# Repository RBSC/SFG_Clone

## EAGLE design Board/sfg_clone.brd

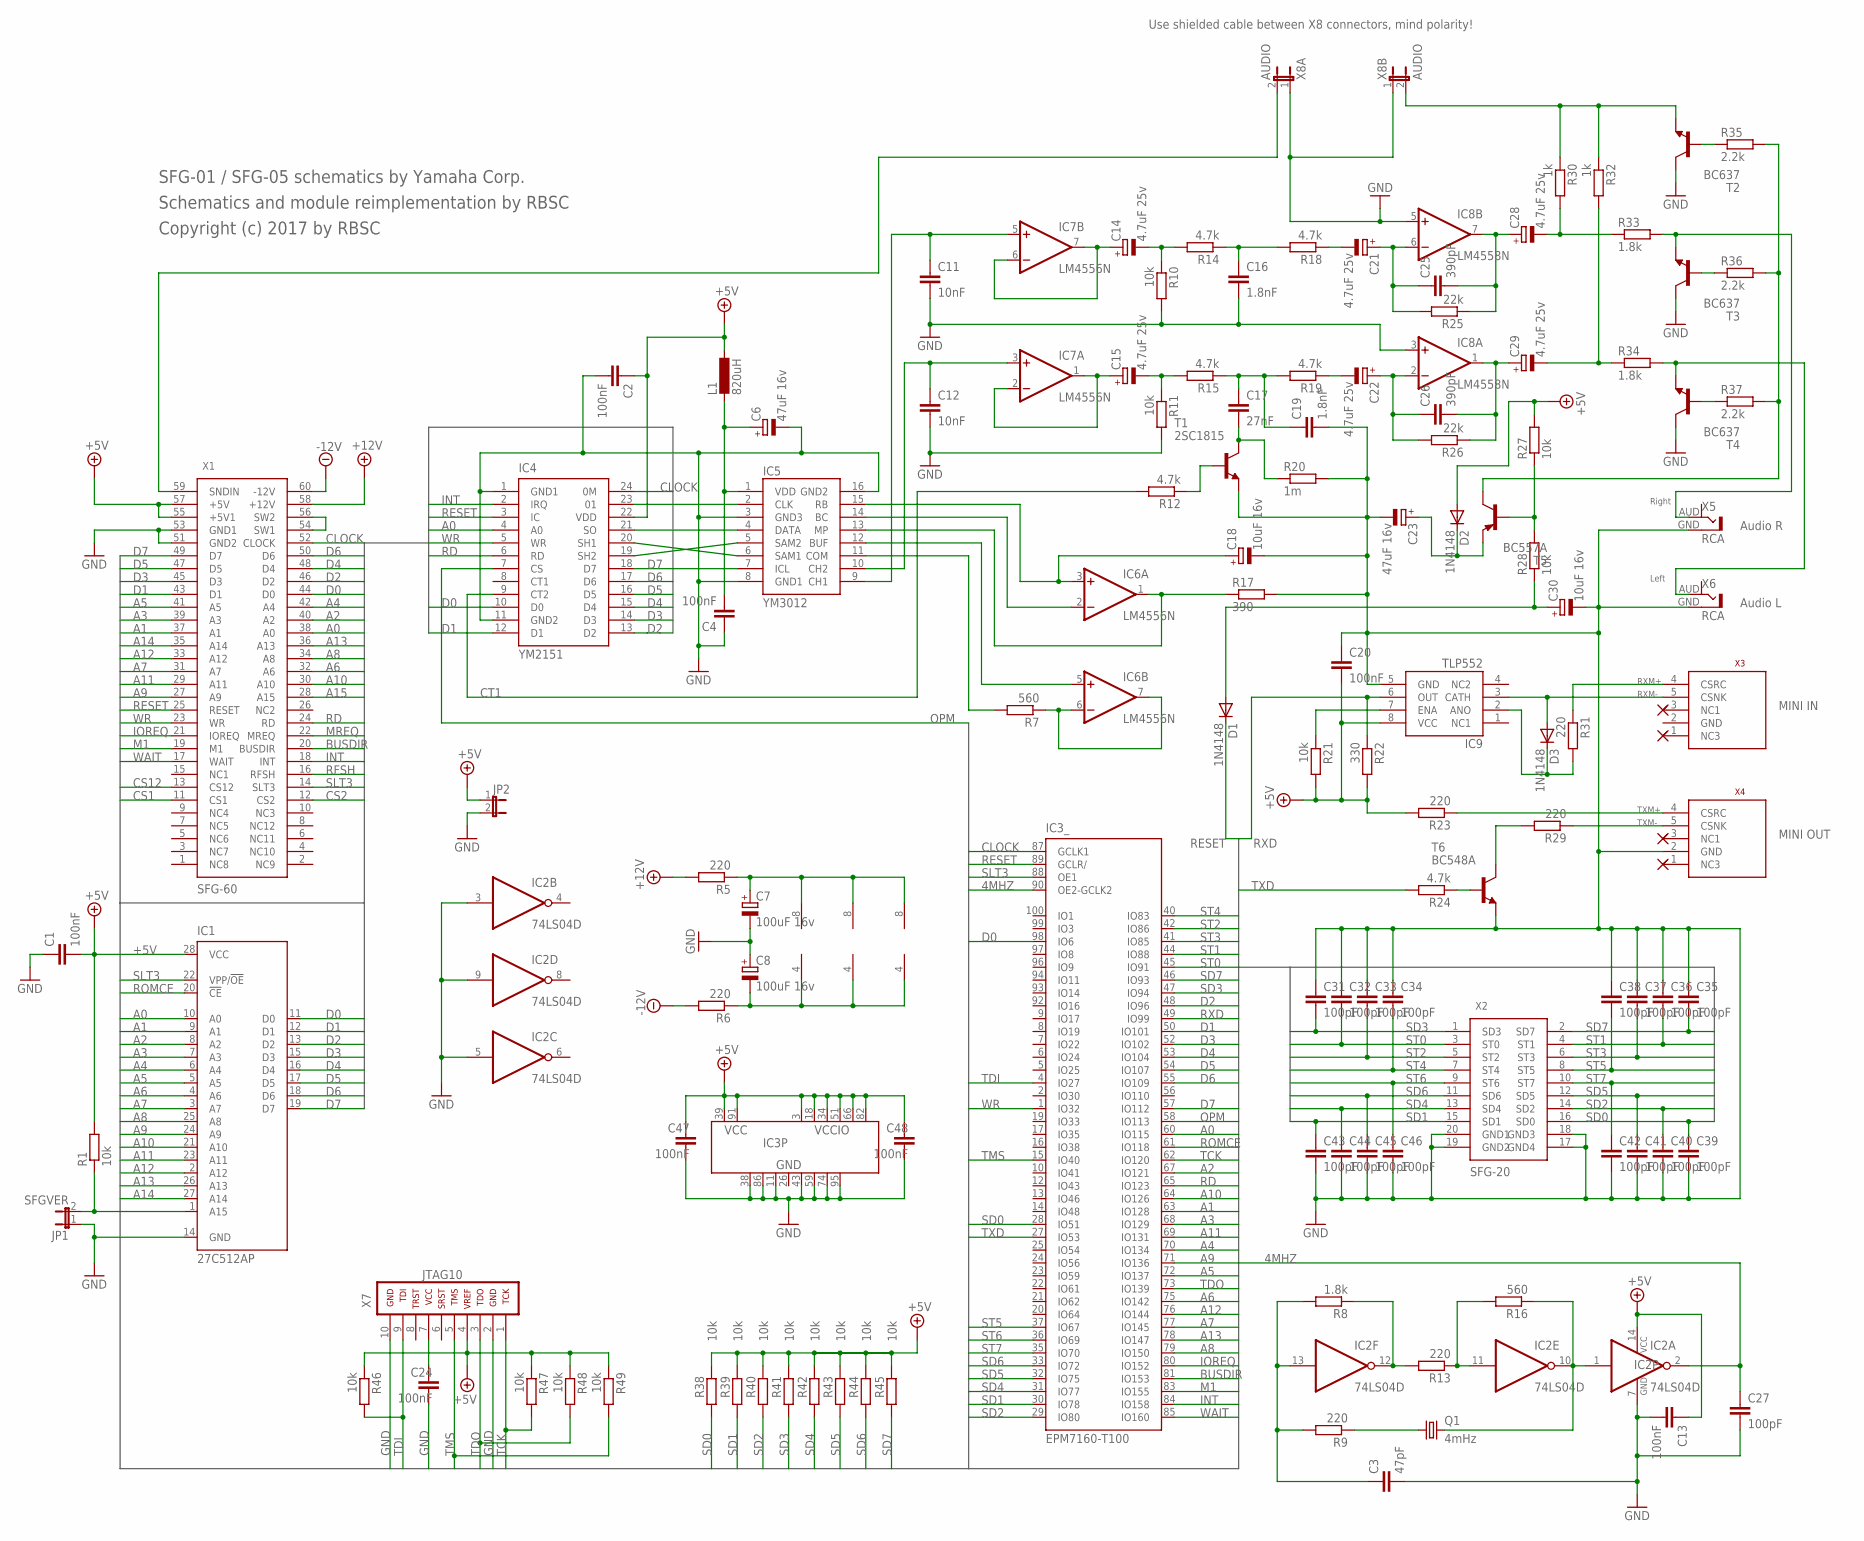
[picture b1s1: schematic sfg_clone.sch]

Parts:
C1, C2, C4, C13, C20, C24, C47, C48: 100nF; C0805
C3: 47pF; C0805
C6, C23: 47uF 16v; SMC_C
C7, C8: 100uF 16v; SMC_D
C11, C12: 10nF; C0805
C14, C15, C21, C22, C28, C29: 4.7uF 25v; SMC_B
C16, C19: 1.8nF; C0805
C17: 27nF; C0805
C18, C30: 10uF 16v; SMC_B
C25, C26: 390pF; C0805
C27, C31, C32, C33, C34, C35, C36, C37, C38, C39, C40, C41, C42, C43, C44, C45, C46: 100pF; C0805
D1, D2, D3: 1N4148; MINIMELF
IC1: 27C512AP; DIL28-6
IC2: 74LS04D; SO14
IC3: EPM7160-T100; TQFP100
IC4: YM2151; DIL24
IC5: YM3012; DIL16
IC6, IC7: LM4556N; DIL08
IC8: LM4558N; DIL08
IC9: TLP552; DIL08
JP1: SFGVER; JP1
JP2: JP1E; JP1
L1: 820uH; 6000-XXXX-RC
Q1: 4mHz; HC49/S
R1, R10, R11, R21, R27, R28, R38, R39, R40, R41, R42, R43, R44, R45, R46, R47, R48, R49: 10k; R0805
R5, R6, R9, R13, R23, R29, R31: 220; R0805
R7, R16: 560; R0805
R8, R33, R34: 1.8k; R0805
R12, R14, R15, R18, R19, R24: 4.7k; R0805
R17: 390; R0805
R20: 1m; R0805
R22: 330; R0805
R25, R26: 22k; R0805
R30, R32: 1k; R0805
R35, R36, R37: 2.2k; R0805
T1: 2SC1815; TO92-ECB
T2, T3, T4: BC637; TO92-ECB
T5: BC557A; TO92-EBC
T6: BC548A; TO92-EBC
X1: SFG-60
X2: SFG-20
X3, X4: MIDI_CONN_FEMALE_SUPPORT; DIN_5_FEMALE_SUPPORT
X5, X6: RCA
X7: JTAG10
X8A, X8B: AUDIO; JP1

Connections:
4MHZ: C27.1, IC2.2 (O), IC3.90 (OE2-GCLK2)
+5V: C1.2, C2.1, C13.1, C20.2, C47.1, C48.1, D2.A, IC1.28 (VCC), IC2.14 (VCC), IC3.3 (VCCIO), IC3.18 (VCCIO), IC3.34 (VCCIO), IC3.39 (VCC), IC3.51 (VCCIO), IC3.66 (VCCIO), IC3.82 (VCCIO), IC3.91 (VCC), IC4.22 (VDD), IC9.8 (VCC), JP2.1, L1.1, R1.2, R21.2, R22.2, R23.2, R27.2, R38.1, R39.1, R40.1, R41.1, R42.1, R43.1, R44.1, R45.1, R46.1, R47.1, R48.1, R49.1, X1.55 (+5V1), X1.57 (+5V), X7.4
+12V: R5.2, X1.58 (+12V)
+12V1: C7.+, IC6.8 (V+), IC7.8 (V+), IC8.8 (V+), R5.1
-12V: R6.2, X1.60 (-12V)
-12V1: C8.-, IC6.4 (V-), IC7.4 (V-), IC8.4 (V-), R6.1
A0: IC1.10 (A0), IC3.60 (IO115), IC4.4 (A0), X1.38 (A0)
A1: IC1.9 (A1), IC3.63 (IO128), X1.37 (A1)
A2: IC1.8 (A2), IC3.67 (IO121), X1.40 (A2)
A3: IC1.7 (A3), IC3.68 (IO129), X1.39 (A3)
A4: IC1.6 (A4), IC3.70 (IO134), X1.42 (A4)
A5: IC1.5 (A5), IC3.72 (IO137), X1.41 (A5)
A6: IC1.4 (A6), IC3.75 (IO142), X1.32 (A6)
A7: IC1.3 (A7), IC3.77 (IO145), X1.31 (A7)
A8: IC1.25 (A8), IC3.79 (IO150), X1.34 (A8)
A9: IC1.24 (A9), IC3.71 (IO136), X1.27 (A9)
A10: IC1.21 (A10), IC3.64 (IO126), X1.30 (A10)
A11: IC1.23 (A11), IC3.69 (IO131), X1.29 (A11)
A12: IC1.2 (A12), IC3.76 (IO144), X1.33 (A12)
A13: IC1.26 (A13), IC3.78 (IO147), X1.36 (A13)
A14: IC1.27 (A14), X1.35 (A14)
A15: X1.28 (A15)
BUSDIR: IC3.81 (IO153), X1.20 (BUSDIR)
CLOCK: IC3.87 (GCLK1), IC4.24 (0M), X1.52 (CLOCK)
CS1: X1.11 (CS1)
CS2: X1.12 (CS2)
CS12: X1.13 (CS12)
CT1: IC4.9 (CT2), R12.2
D0: IC1.11 (D0), IC3.98 (IO6), IC4.10 (D0), X1.44 (D0)
D1: IC1.12 (D1), IC3.50 (IO101), IC4.12 (D1), X1.43 (D1)
D2: IC1.13 (D2), IC3.48 (IO96), IC4.13 (D2), X1.46 (D2)
D3: IC1.15 (D3), IC3.52 (IO102), IC4.14 (D3), X1.45 (D3)
D4: IC1.16 (D4), IC3.53 (IO104), IC4.15 (D4), X1.48 (D4)
D5: IC1.17 (D5), IC3.54 (IO107), IC4.16 (D5), X1.47 (D5)
D6: IC1.18 (D6), IC3.55 (IO109), IC4.17 (D6), X1.50 (D6)
D7: IC1.19 (D7), IC3.57 (IO112), IC4.18 (D7), X1.49 (D7)
GND: C1.1, C2.2, C3.2, C4.1, C6.-, C7.-, C8.+, C11.2, C12.2, C13.2, C16.2, C18.-, C19.2, C20.1, C23.-, C24.2, C27.2, C30.-, C31.1, C32.1, C33.1, C34.1, C35.1, C36.1, C37.1, C38.1, C39.2, C40.2, C41.2, C42.2, C43.2, C44.2, C45.2, C46.2, C47.2, C48.2, IC1.14 (GND), IC2.3 (I), IC2.5 (I), IC2.7 (GND), IC2.9 (I), IC3.11 (GND), IC3.26 (GND), IC3.38 (GND), IC3.43 (GND), IC3.59 (GND), IC3.74 (GND), IC3.86 (GND), IC3.95 (GND), IC4.1 (GND1), IC4.11 (GND2), IC5.3 (GND3), IC5.8 (GND1), IC5.16 (GND2), IC8.3 (+IN), IC8.5 (+IN), IC9.5 (GND), JP1.1, JP2.2, R10.2, R11.2, R17.2, R20.2, T1.E, T2.C, T3.C, T4.C, T6.E, X1.51 (GND2), X1.53 (GND1), X2.17 (GND4), X2.18 (GND3), X2.19 (GND2), X2.20 (GND1), X4.2 (GND), X5.GND (GND1), X6.GND (GND1), X7.2, X7.10, X8A.1, X8B.1
INT: IC3.84 (IO158), IC4.2 (IRQ), X1.18 (INT)
IOREQ: IC3.80 (IO152), X1.21 (IOREQ)
M1: IC3.83 (IO155), X1.19 (M1)
MREQ: X1.22 (MREQ)
unnamed: IC1.1 (A15), JP1.2, R1.1
unnamed: C24.1, X7.7
unnamed: X1.54 (SW1), X1.56 (SW2)
unnamed: R30.1, R32.1, T2.E, X8B.2
unnamed: X1.59 (SNDIN), X8A.2
unnamed: C3.1, IC2.13 (I), R8.2, R9.2
unnamed: IC2.12 (O), R8.1, R13.2
unnamed: IC2.1 (I), IC2.10 (O), Q1.2, R16.1
unnamed: Q1.1, R9.1
unnamed: IC2.11 (I), R13.1, R16.2
unnamed: R24.1, T6.B
unnamed: R29.2, T6.C
unnamed: R29.1, X4.5 (CSNK)
unnamed: R23.1, X4.4 (CSRC)
unnamed: D3.A, IC9.3 (CATH), X3.5 (CSNK)
unnamed: R31.1, X3.4 (CSRC)
unnamed: IC9.7 (ENA), R21.1
unnamed: D3.C, IC9.2 (ANO), R31.2
unnamed: IC4.23 (01), IC5.2 (CLK)
unnamed: IC4.21 (SO), IC5.4 (DATA)
unnamed: C28.-, R30.2, R33.1
unnamed: IC4.20 (SH1), IC5.6 (SAM1)
unnamed: C4.2, C6.+, IC5.1 (VDD), L1.2
unnamed: IC4.19 (SH2), IC5.5 (SAM2)
unnamed: IC6.6 (-IN), IC6.7 (OUT), R7.1
unnamed: IC5.11 (COM), R7.2
unnamed: C12.1, IC5.10 (CH2), IC7.3 (+IN)
unnamed: IC5.12 (BUF), IC6.5 (+IN)
unnamed: IC5.13 (MP), IC6.1 (OUT), R17.1
unnamed: C18.+, IC5.15 (RB), IC6.3 (+IN)
unnamed: C21.+, C25.1, IC8.6 (-IN), R25.2
unnamed: C14.+, IC7.6 (-IN), IC7.7 (OUT)
unnamed: C15.+, IC7.1 (OUT), IC7.2 (-IN)
unnamed: C11.1, IC5.9 (CH1), IC7.5 (+IN)
unnamed: C14.-, R10.1, R14.2
unnamed: C15.-, R11.1, R15.2
unnamed: IC5.14 (BC), IC6.2 (-IN)
unnamed: C17.2, R20.1, T1.C
unnamed: C16.1, R14.1, R18.2
unnamed: C17.1, C19.1, R15.1, R19.2
unnamed: C22.+, C26.1, IC8.2 (-IN), R26.2
unnamed: C22.-, R19.1
unnamed: C21.-, R18.1
unnamed: R12.1, T1.B
unnamed: C26.2, C29.+, IC8.1 (OUT), R26.1
unnamed: C25.2, C28.+, IC8.7 (OUT), R25.1
unnamed: C29.-, R32.2, R34.1
unnamed: R33.2, T3.E, X5.AUD
unnamed: R34.2, T4.E, X6.AUD
unnamed: R35.1, T2.B
unnamed: R35.2, R36.2, R37.2, T5.C
unnamed: R36.1, T3.B
unnamed: R37.1, T4.B
unnamed: C30.+, D1.A, R28.1
unnamed: C23.+, D2.C, T5.E
unnamed: R27.1, R28.2, T5.B
OPM: IC3.58 (IO113), IC4.7 (CS)
RD: IC3.65 (IO123), IC4.6 (RD), X1.24 (RD)
RESET: D1.C, IC3.89 (GCLR/), IC4.3 (IC), IC5.7 (ICL), X1.25 (RESET)
RFSH: X1.16 (RFSH)
ROMCE: IC1.20 (!CE), IC3.61 (IO118)
RXD: IC3.49 (IO99), IC9.6 (OUT), R22.1
SD0: C39.1, IC3.28 (IO51), R38.2, X2.16 (SD0)
SD1: C43.1, IC3.30 (IO78), R39.2, X2.15 (SD1)
SD2: C40.1, IC3.29 (IO80), R40.2, X2.14 (SD2)
SD3: C31.2, IC3.47 (IO94), R41.2, X2.1 (SD3)
SD4: C44.1, IC3.31 (IO77), R42.2, X2.13 (SD4)
SD5: C41.1, IC3.32 (IO75), R43.2, X2.12 (SD5)
SD6: C45.1, IC3.33 (IO72), R44.2, X2.11 (SD6)
SD7: C35.2, IC3.46 (IO93), R45.2, X2.2 (SD7)
SLT3: IC1.22 (VPP/!OE), IC3.88 (OE1), X1.14 (SLT3)
ST0: C32.2, IC3.45 (IO91), X2.3 (ST0)
ST1: C36.2, IC3.44 (IO88), X2.4 (ST1)
ST2: C33.2, IC3.42 (IO86), X2.5 (ST2)
ST3: C37.2, IC3.41 (IO85), X2.6 (ST3)
ST4: C34.2, IC3.40 (IO83), X2.7 (ST4)
ST5: C38.2, IC3.37 (IO67), X2.8 (ST5)
ST6: C46.1, IC3.36 (IO69), X2.9 (ST6)
ST7: C42.1, IC3.35 (IO70), X2.10 (ST7)
TCK: IC3.62 (IO120), R47.2, X7.1
TDI: IC3.4 (IO27), R46.2, X7.9
TDO: IC3.73 (IO139), R48.2, X7.3
TMS: IC3.15 (IO40), R49.2, X7.5
TXD: IC3.27 (IO53), R24.2
WAIT: IC3.85 (IO160), X1.17 (WAIT)
WR: IC3.1 (IO32), IC4.5 (WR), X1.23 (WR)

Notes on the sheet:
Use shielded cable between X8 connectors, mind polarity!
SFG-01 / SFG-05 schematics by Yamaha Corp.
Schematics and module reimplementation by RBSC
Copyright (c) 2017 by RBSC
Audio R
Audio L
MINI IN
MINI OUT
RXM+
RXM-
TXM-
TXM+
Right
Left

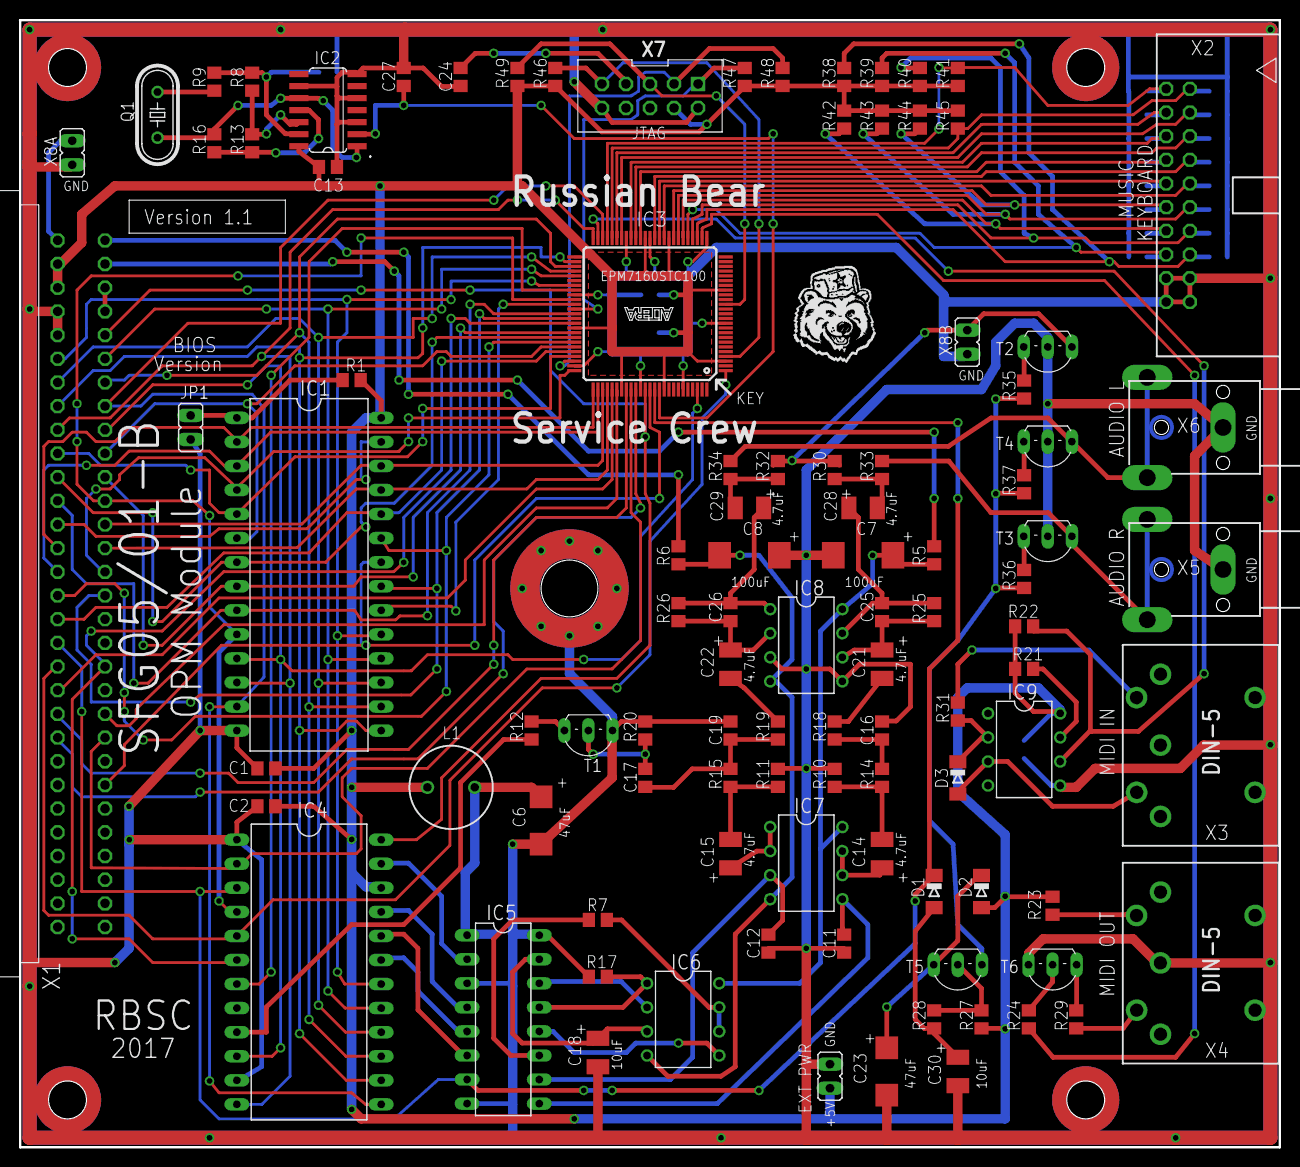
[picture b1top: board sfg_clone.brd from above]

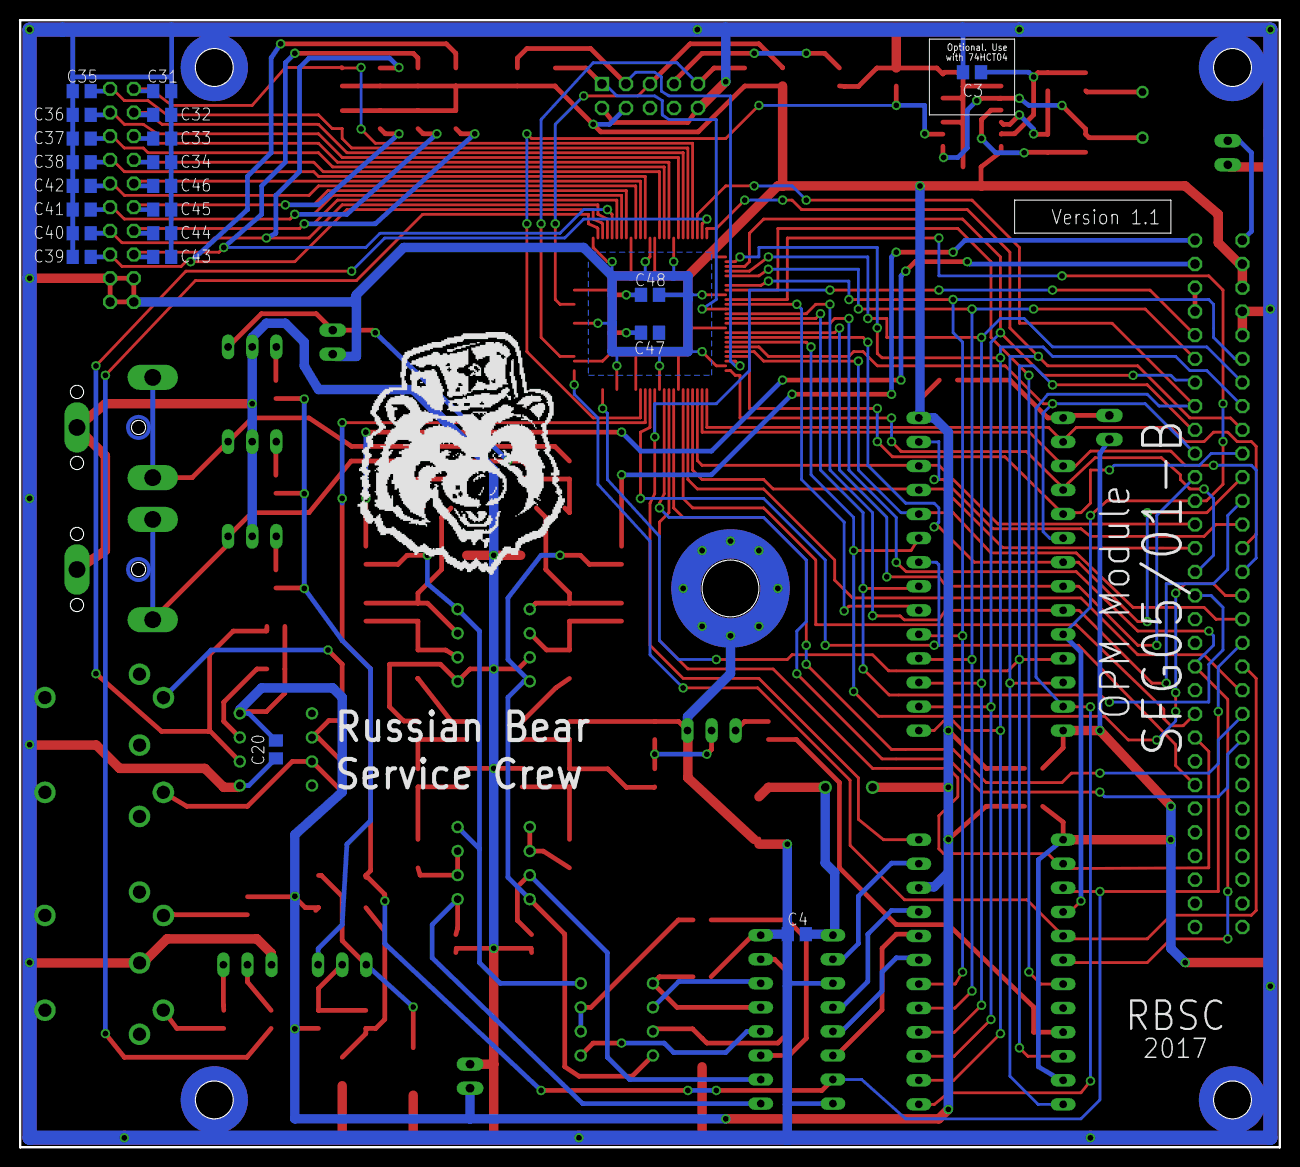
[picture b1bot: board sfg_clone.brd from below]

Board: 2 copper layers, 133.0 x 119.0 mm, 122 parts (21 on the bottom side), 121 nets.

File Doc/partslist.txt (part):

SFG 05/01-B Clone Version 1.1
Copyright (C) 2017 RBSC
Copyright (C) Yamaha Corporation
--------------------------------

Assembly variant: 

Part     Value                    Device                   Package              Library             Sheet

C1       100nF                    C-EUC0805                C0805                rcl                 1
C2       100nF                    C-EUC0805                C0805                rcl                 1
C3       47pF                     C-EUC0805                C0805                rcl                 1
C4       100nF                    C-EUC0805                C0805                rcl                 1
C6       47uF 16v                 CPOL-EUSMCC              SMC_C                rcl                 1
C7       100uF 16v                CPOL-EUSMCD              SMC_D                rcl                 1
C8       100uF 16v                CPOL-EUSMCD              SMC_D                rcl                 1
C11      10nF                     C-EUC0805                C0805                rcl                 1
C12      10nF                     C-EUC0805                C0805                rcl                 1
C13      100nF                    C-EUC0805                C0805                rcl                 1
C14      4.7uF 25v                CPOL-EUSMCB              SMC_B                rcl                 1
C15      4.7uF 25v                CPOL-EUSMCB              SMC_B                rcl                 1
C16      1.8nF                    C-EUC0805                C0805                rcl                 1
C17      27nF                     C-EUC0805                C0805                rcl                 1
C18      10uF 16v                 CPOL-EUSMCB              SMC_B                rcl                 1
C19      1.8nF                    C-EUC0805                C0805                rcl                 1
C20      100nF                    C-EUC0805                C0805                rcl                 1
C21      4.7uF 25v                CPOL-EUSMCB              SMC_B                rcl                 1
C22      4.7uF 25v                CPOL-EUSMCB              SMC_B                rcl                 1
C23      47uF 16v                 CPOL-EUSMCC              SMC_C                rcl                 1
C24      100nF                    C-EUC0805                C0805                rcl                 1
C25      390pF                    C-EUC0805                C0805                rcl                 1
C26      390pF                    C-EUC0805                C0805                rcl                 1
C27      100pF                    C-EUC0805                C0805                rcl                 1
C28      4.7uF 25v                CPOL-EUSMCB              SMC_B                rcl                 1
C29      4.7uF 25v                CPOL-EUSMCB              SMC_B                rcl                 1
C30      10uF 16v                 CPOL-EUSMCB              SMC_B                rcl                 1
C31      100pF                    C-EUC0805                C0805                rcl                 1
C32      100pF                    C-EUC0805                C0805                rcl                 1
C33      100pF                    C-EUC0805                C0805                rcl                 1
C34      100pF                    C-EUC0805                C0805                rcl                 1
C35      100pF                    C-EUC0805                C0805                rcl                 1
C36      100pF                    C-EUC0805                C0805                rcl                 1
C37      100pF                    C-EUC0805                C0805                rcl                 1
C38      100pF                    C-EUC0805                C0805                rcl                 1
C39      100pF                    C-EUC0805                C0805                rcl                 1
C40      100pF                    C-EUC0805                C0805                rcl                 1
C41      100pF                    C-EUC0805                C0805                rcl                 1
C42      100pF                    C-EUC0805                C0805                rcl                 1
C43      100pF                    C-EUC0805                C0805                rcl                 1
C44      100pF                    C-EUC0805                C0805                rcl                 1
C45      100pF                    C-EUC0805                C0805                rcl                 1
C46      100pF                    C-EUC0805                C0805                rcl                 1
C47      100nF                    C-EUC0805                C0805                rcl                 1
C48      100nF                    C-EUC0805                C0805                rcl                 1
D1       1N4148                   DIODE-MINIMELF           MINIMELF             diode               1
D2       1N4148                   DIODE-MINIMELF           MINIMELF             diode               1
D3       1N4148                   DIODE-MINIMELF           MINIMELF             diode               1
IC1      27C512AP                 27C512AP                 DIL28-6              microchip           1
IC2      74LS04D                  74LS04D                  SO14                 74xx-eu             1
IC3      EPM7160-T100             EPM7160-T100             TQFP100              altera              1
IC4      YM2151                   YM2151                   DIL24                ym2151              1
IC5      YM3012                   YM3012                   DIL16                ym3012              1
IC6      LM4556N                  LM4556N                  DIL08                LM4556              1
IC7      LM4556N                  LM4556N                  DIL08                LM4556              1
IC8      LM4558N                  LM4558N                  DIL08                LM4558              1
IC9      TLP552                   TLP552                   DIL08                TLP552              1
JP1      SFGVER                   JP1E                     JP1                  jumper              1
JP2                               JP1E                     JP1                  jumper              1
L1       820uH                    L-EU6000-XXX-RC          6000-XXXX-RC         rcl                 1
Q1       4mHz                     CRYSTALHC49S             HC49/S               crystal             1
R1       10k                      R-EU_R0805               R0805                resistor            1
R5       220                      R-EU_R0805               R0805                resistor            1
R6       220                      R-EU_R0805               R0805                resistor            1
R7       560                      R-EU_R0805               R0805                resistor            1
R8       1.8k                     R-EU_R0805               R0805                resistor            1
R9       220                      R-EU_R0805               R0805                resistor            1
R10      10k                      R-EU_R0805               R0805                resistor            1
R11      10k                      R-EU_R0805               R0805                resistor            1
R12      4.7k                     R-EU_R0805               R0805                resistor            1
R13      220                      R-EU_R0805               R0805                resistor            1
R14      4.7k                     R-EU_R0805               R0805                resistor            1
R15      4.7k                     R-EU_R0805               R0805                resistor            1
R16      560                      R-EU_R0805               R0805                resistor            1
R17      390                      R-EU_R0805               R0805                resistor            1
R18      4.7k                     R-EU_R0805               R0805                resistor            1
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
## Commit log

2016-05-29 :boom::camel: Added .gitattributes & .gitignore files
2016-05-29 Initial files
2016-06-02 Board picture
2017-03-28 First major commit
    New board revision, schematics, Gerbers
2017-05-07 The sources for v1.0 board
2017-05-20 Added firmware files
2017-05-21 Firmware readme added
2017-06-11 New pics of the module
2017-06-11 Removed small pic
2017-07-10 Board updated to version 1.1
    Board updated to version 1.1
2018-08-07 Updated readme 07.08.2018
    Updated readme 07.08.2018
2018-12-08 Release 08.12.2018
    SFG module case (RBSC version)
2018-12-08 Release 08.12.2018
    Added front panel model to be used with the network module case
2019-03-28 Updated 28.03.2019
    Reduced screw holes by 1mm.
2019-05-01 Updated 01.05.2019
    3D model of the case added, use Fusion 360
2021-01-22 Updated 21.01.2021
    Fixed schematics and partslist (the value of the coil was incorrectly
    specified)

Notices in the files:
parts and their libraries:
SparkFun-Connectors: Licensing: Creative Commons ShareAlike 4.0 International - https://creativecommons.org/licenses/by-sa/4.0
ym3012: YM3012>Created by RBSC>(c) 2016>
TLP552: Created by RBSC>(c) 2016>
ym2151: YM2151>Created by RBSC>(c) 2016>
